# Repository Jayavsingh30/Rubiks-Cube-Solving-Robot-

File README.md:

https://github.com/user-attachments/assets/8eff1edc-73fc-4dad-ae04-fb5bdb494c74

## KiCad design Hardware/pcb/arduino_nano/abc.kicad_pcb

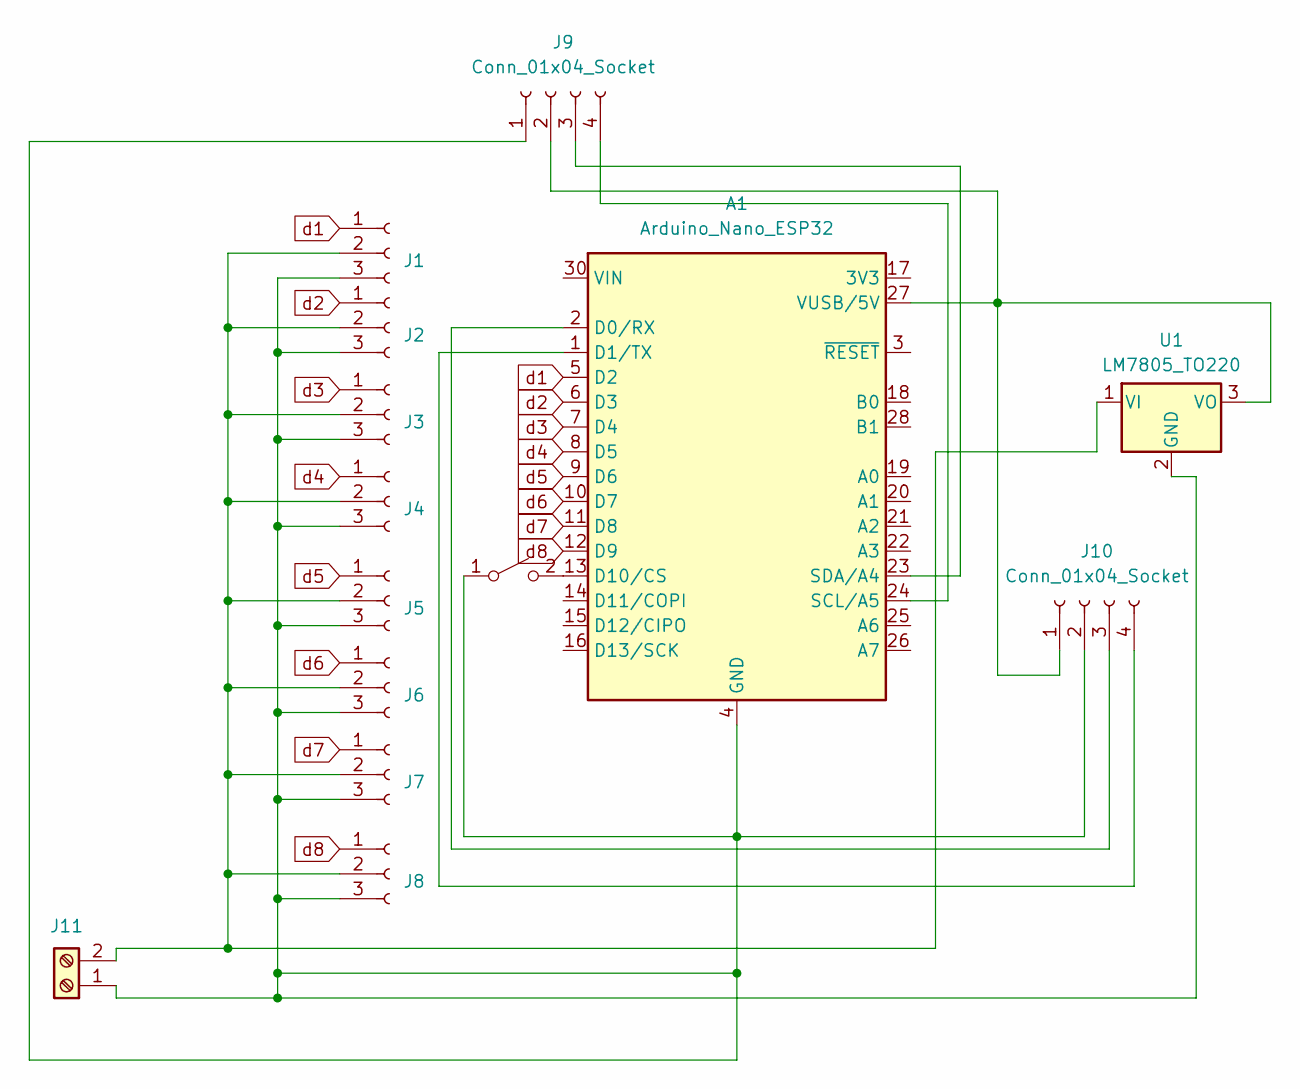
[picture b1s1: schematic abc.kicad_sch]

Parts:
A1: Arduino_Nano_ESP32; Arduino_Nano
J1, J2, J3, J4, J5, J6, J7, J8: Conn_01x03_Socket; PinHeader_1x03_P2.54mm_Vertical
J9, J10: Conn_01x04_Socket; PinHeader_1x04_P2.54mm_Vertical
J11: Screw_Terminal_01x02; TerminalBlock_Phoenix_MKDS-1,5-2-5.08_1x02_P5.08mm_Horizont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
SW1: SW_SPST; SW_PUSH_6mm_H4.3mm
U1: LM7805_TO220; TO-220-3_Vertical

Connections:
unnamed: A1.2 (D0/RX), J10.3
unnamed: A1.1 (D1/TX), J10.4
unnamed: A1.13 (D10/CS), SW1.2 (B)
unnamed: A1.24 (SCL/A5), J9.4
unnamed: A1.23 (SDA/A4), J9.3
unnamed: A1.27 (VUSB/5V), J9.2, J10.1, U1.3 (VO)
unnamed: J1.2, J2.2, J3.2, J4.2, J5.2, J6.2, J7.2, J8.2, J11.2, U1.1 (VI)
unnamed: A1.4 (GND), A1.29 (GND), J1.3, J2.3, J3.3, J4.3, J5.3, J6.3, J7.3, J8.3, J9.1, J10.2, J11.1, SW1.1 (A), U1.2 (GND)
d1: A1.5 (D2), J1.1
d2: A1.6 (D3), J2.1
d3: A1.7 (D4), J3.1
d4: A1.8 (D5), J4.1
d5: A1.9 (D6), J5.1
d6: A1.10 (D7), J6.1
d7: A1.11 (D8), J7.1
d8: A1.12 (D9), J8.1

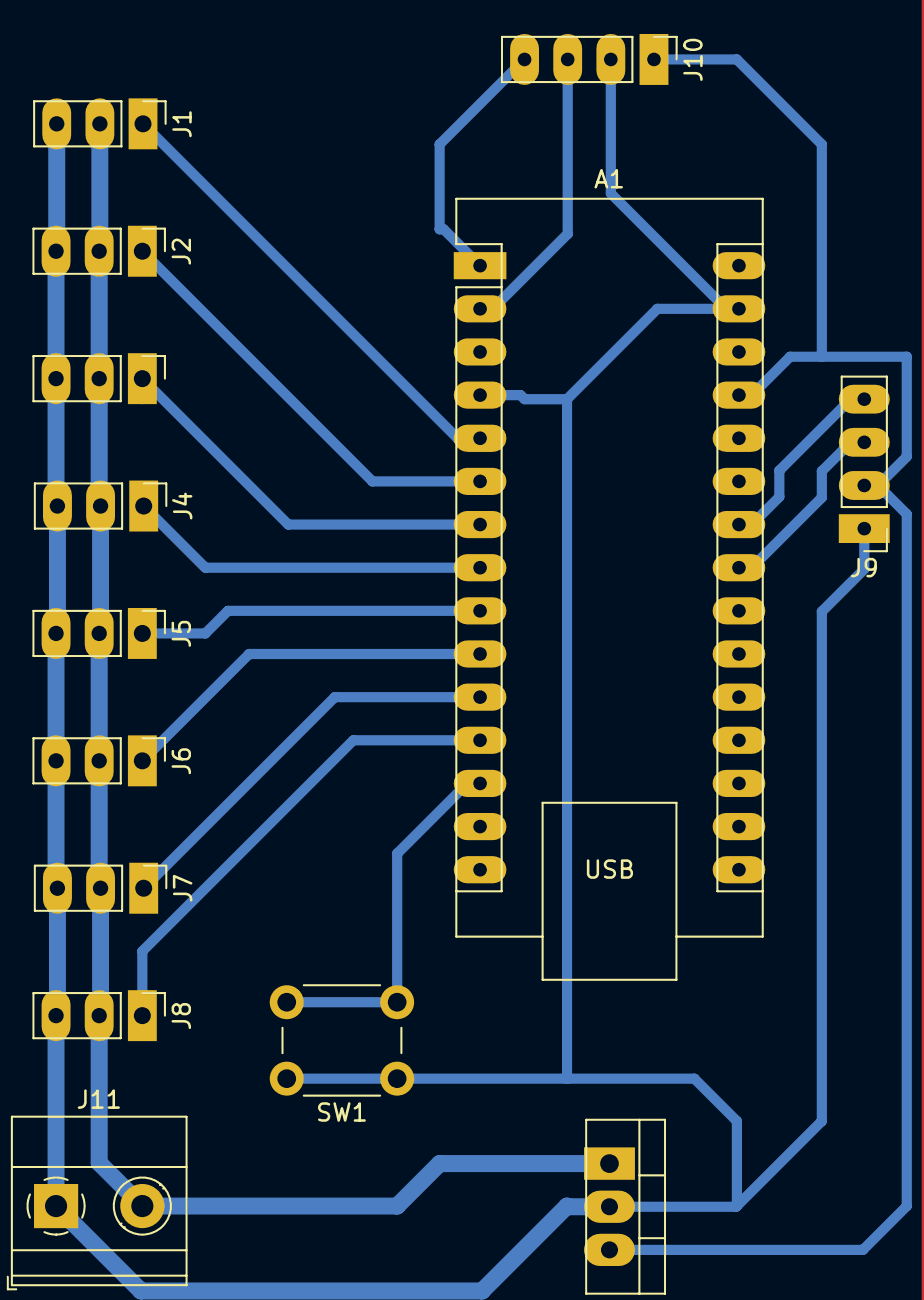
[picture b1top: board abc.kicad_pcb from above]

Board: 2 copper layers, 14 parts (0 on the bottom side), 16 nets.

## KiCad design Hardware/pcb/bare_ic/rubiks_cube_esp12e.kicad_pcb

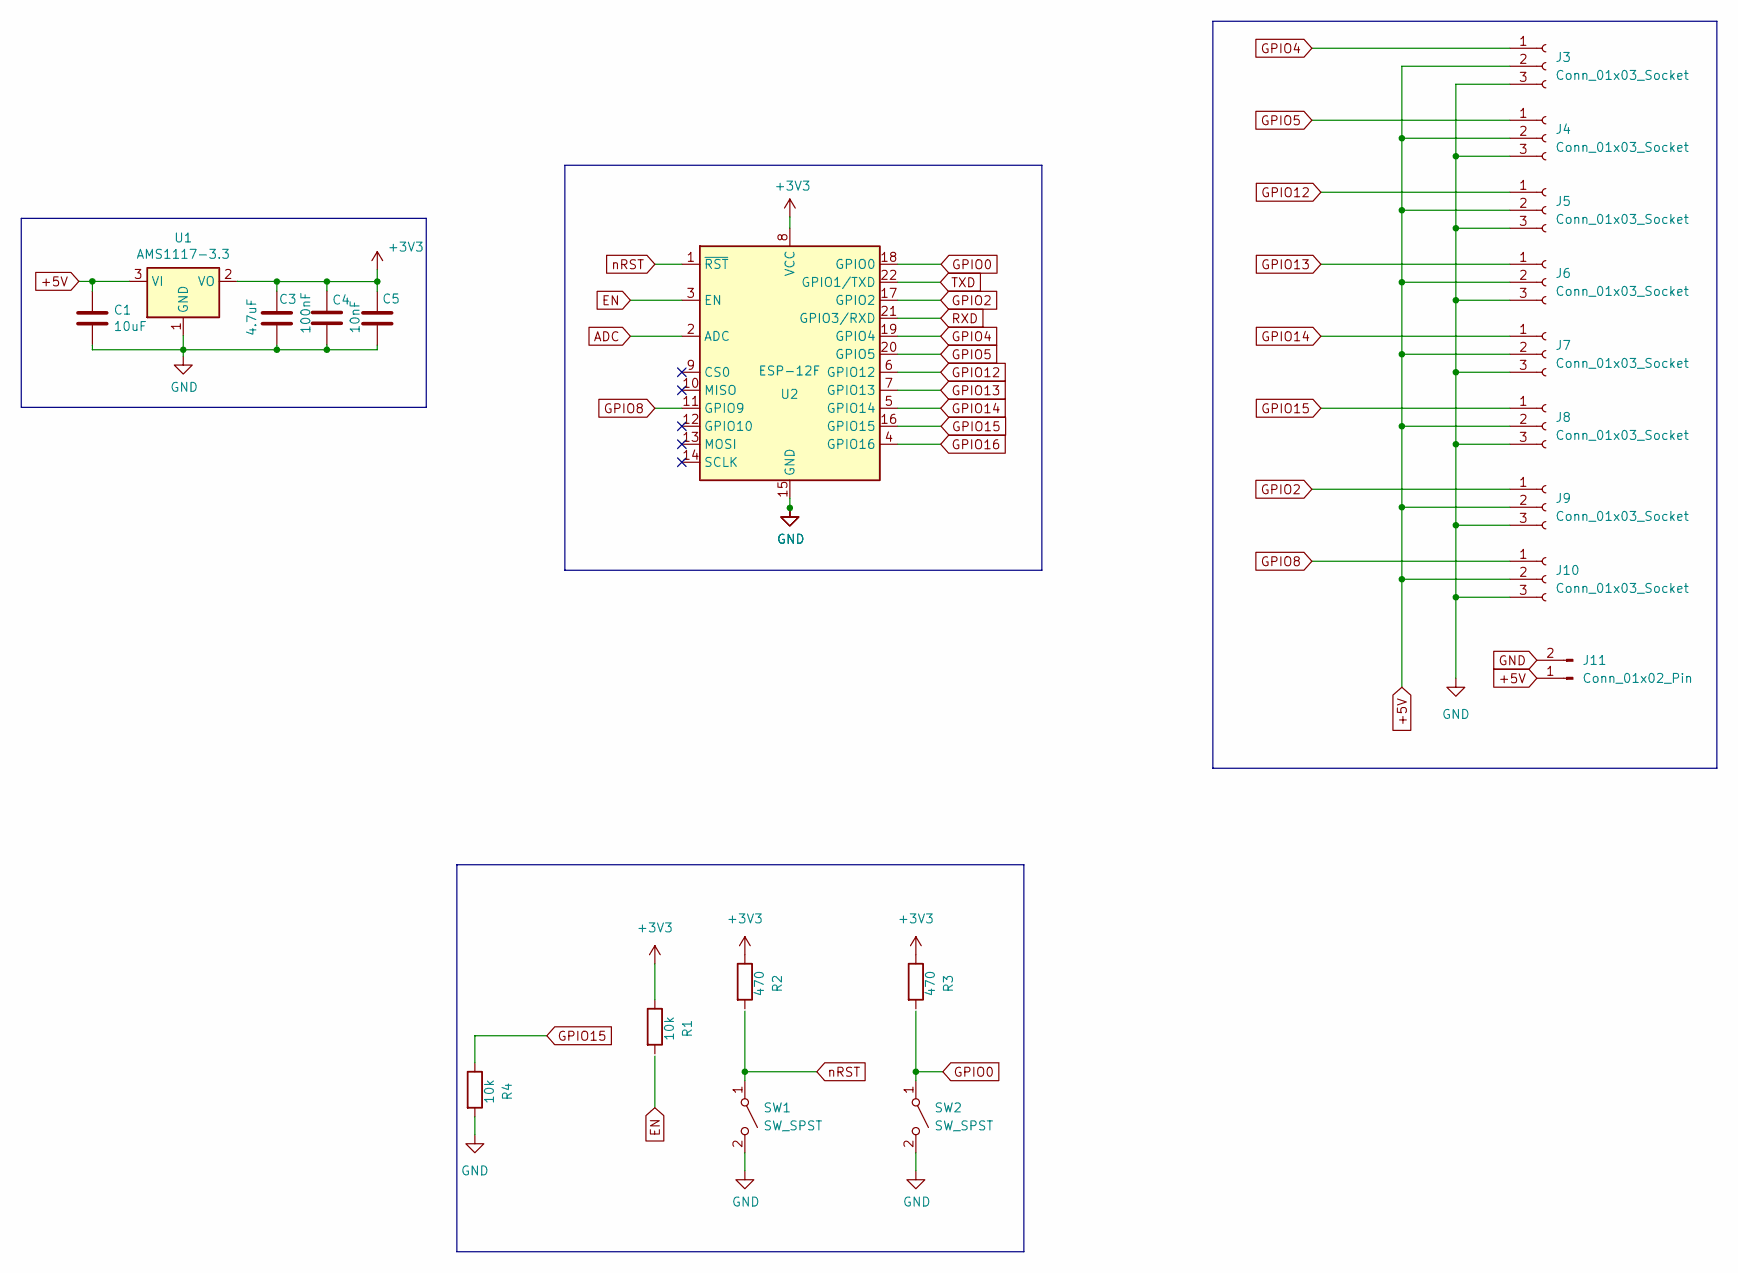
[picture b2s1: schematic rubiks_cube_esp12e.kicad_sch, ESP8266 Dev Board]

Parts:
C1: 10uF; C_0805_2012Metric_Pad1.18x1.45mm_HandSolder
C3: 4.7uF; C_0805_2012Metric_Pad1.18x1.45mm_HandSolder
C4: 100nF; C_0805_2012Metric_Pad1.18x1.45mm_HandSolder
C5: 10nF; C_0805_2012Metric_Pad1.18x1.45mm_HandSolder
J3, J4, J5, J6, J7, J8, J9, J10: Conn_01x03_Socket; PinHeader_1x03_P2.54mm_Vertical
J11: Conn_01x02_Pin; TerminalBlock_Phoenix_MKDS-1,5-2-5.08_1x02_P5.08mm_Horizont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
R1, R4: 10k; R_0805_2012Metric
R2, R3: 470; R_0805_2012Metric
SW1, SW2: SW_SPST; SW_PUSH_6mm_H5mm
U1: AMS1117-3.3; SOT-223-3_TabPin2
U2: ESP-12F; ESP-12E

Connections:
+3V3: C3.1, C4.1, C5.1, R1.1, R2.1, R3.1, U1.2 (VO), U2.8 (VCC)
+5V: C1.1, J3.2, J4.2, J5.2, J6.2, J7.2, J8.2, J9.2, J10.2, J11.1, U1.3 (VI)
ADC: U2.2 (ADC)
EN: U2.3 (EN)
GND: C1.2, C3.2, C4.2, C5.2, J3.3, J4.3, J5.3, J6.3, J7.3, J8.3, J9.3, J10.3, J11.2, R4.2, SW1.2 (B), SW2.2 (B), U1.1 (GND), U2.15 (GND)
GPIO0: SW2.1 (A), U2.18 (GPIO0)
GPIO2: J9.1, U2.17 (GPIO2)
GPIO4: J3.1, U2.19 (GPIO4)
GPIO5: J4.1, U2.20 (GPIO5)
GPIO8: J10.1, U2.11 (GPIO9)
GPIO12: J5.1, U2.6 (GPIO12)
GPIO13: J6.1, U2.7 (GPIO13)
GPIO14: J7.1, U2.5 (GPIO14)
GPIO15: J8.1, R4.1, U2.16 (GPIO15)
GPIO16: U2.4 (GPIO16)
RXD: U2.21 (GPIO3/RXD)
TXD: U2.22 (GPIO1/TXD)
nRST: SW1.1 (A), U2.1 (~RST)

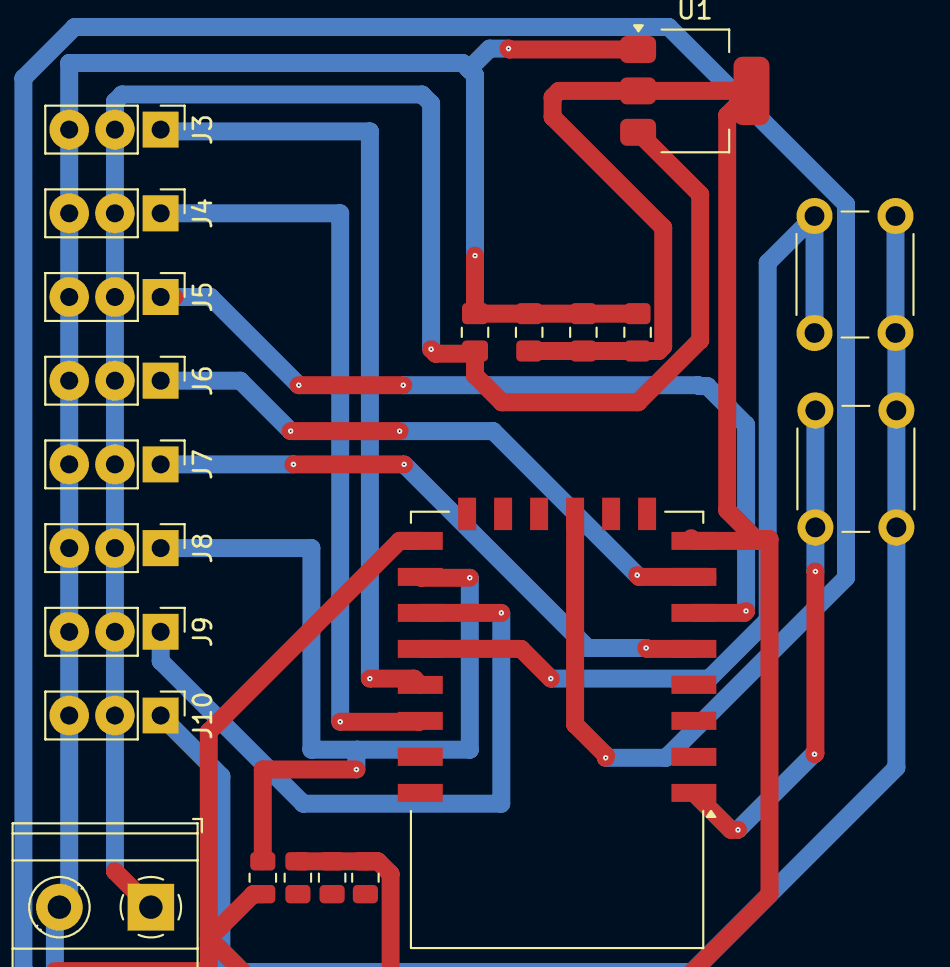
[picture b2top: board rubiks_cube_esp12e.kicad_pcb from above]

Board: 2 copper layers, 21 parts (0 on the bottom side), 13 nets.

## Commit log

2025-05-21 rubix cube cpp file
